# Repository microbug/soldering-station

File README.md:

# Soldering Station (Richard's Version)
A JBC-compatible open-source soldering station. Built for T245 tips.

## Hardware

## Firmware
An STM32CubeIDE project targetting an STM32L011F4Px.

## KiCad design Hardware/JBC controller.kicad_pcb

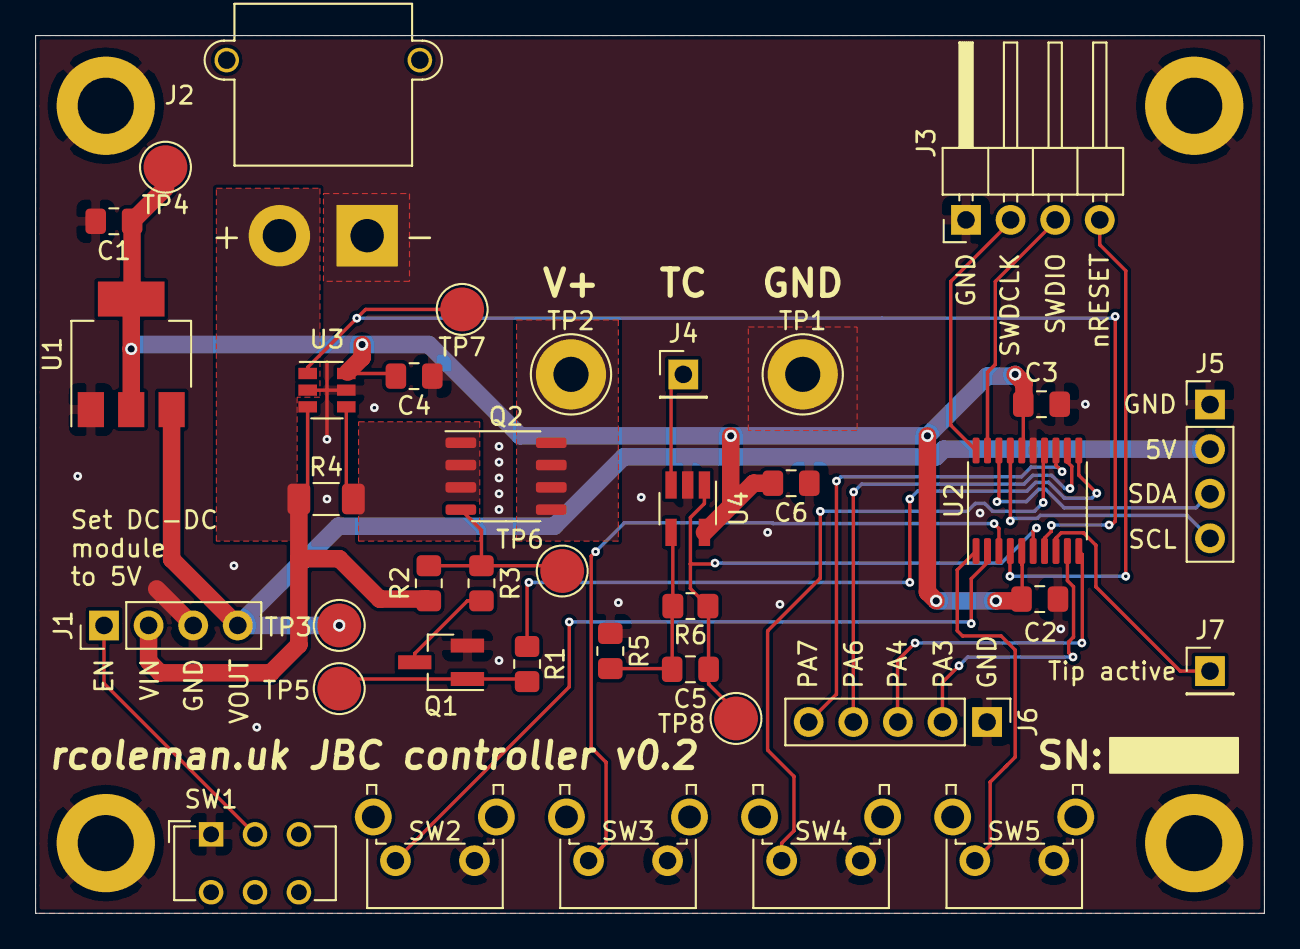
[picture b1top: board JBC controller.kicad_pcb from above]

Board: 2 copper layers, 70.0 x 50.0 mm, 42 parts (0 on the bottom side), 29 nets.

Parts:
C1: 10u; C_0805_2012Metric_Pad1.18x1.45mm_HandSolder
C2, C3, C4, C6: 100n; C_0805_2012Metric_Pad1.18x1.45mm_HandSolder
C5: 1n; C_0805_2012Metric_Pad1.18x1.45mm_HandSolder
H1, H2, H3, H4: MountingHole_Pad; MountingHole_3.2mm_M3_DIN965_Pad
J1, J5: Conn_01x04_Male; PinHeader_1x04_P2.54mm_Vertical
J2: XT30; AMASS_XT30PW-M_1x02_P2.50mm_Horizontal
J3: Conn_01x04_Male; PinHeader_1x04_P2.54mm_Horizontal
J4, J7: Conn_01x01_Male; PinHeader_1x01_P2.54mm_Vertical
J6: Conn_01x05_Male; PinHeader_1x05_P2.54mm_Vertical
Q1: BC846; SOT-23_Handsoldering
Q2: SI4101DY
R1: 10k; R_0805_2012Metric_Pad1.20x1.40mm_HandSolder
R2: 470; R_0805_2012Metric_Pad1.20x1.40mm_HandSolder
R3: 2k2; R_0805_2012Metric_Pad1.20x1.40mm_HandSolder
R4: 10m; R_1206_3216Metric_Pad1.30x1.75mm_HandSolder
R5: 100; R_0805_2012Metric_Pad1.20x1.40mm_HandSolder
R6: 20k; R_0805_2012Metric_Pad1.20x1.40mm_HandSolder
SW1: JS202011AQN; SW_CuK_JS202011AQN_DPDT_Angled
SW2, SW3, SW4, SW5: FSMRA3JH; SW_Tactile_SPST_Angled_PTS645Vx58-2LFS
TP1, TP2: TestPoint; TestPoint_Plated_Hole_D3.0mm
TP3, TP4, TP5, TP6, TP7, TP8: TestPoint; TestPoint_Pad_D2.5mm
U1: LM1117-3.3; SOT-223-3_TabPin2
U2: STM32L011F4Px; TSSOP-20_4.4x6.5mm_P0.65mm
U3: INA181A1; SOT-23-6
U4: AD8538AR; SOT-23-5_HandSoldering

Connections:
+3V3: C1.1, C2.1, C3.2, C4.2, C6.2, TP4.1, U1.2, U2.5, U2.16, U3.6, U4.5
+5V: J1.4, J5.2, TP3.1, U1.3
/BTN_DOWN: SW4.2, U2.14
/BTN_ENTER: SW5.2, U2.1
/BTN_MENU: SW2.2, U2.2
/BTN_UP: SW3.2, U2.3
/HEATER_CURRENT_AMP: TP7.1, U2.7, U3.1
/I2C_SCL: J5.4, U2.17
/I2C_SDA: J5.3, U2.18
/NRESET: J3.4, U2.4
/PA3: J6.2, U2.9
/PA4: J6.3, U2.10
/PA6: J6.4, U2.12
/PA7: J6.5, U2.13
/SWDCLK: J3.2, U2.20
/SWDIO: J3.3, U2.19
/TIP_ACTIVE: J7.1, U2.8
/TIP_PWM: R1.2, U2.11
/TIP_TC: J4.1, U4.3
/TIP_TC_AMP: C5.1, R6.1, TP8.1, U2.6, U4.1
/TIP_V+: Q2.3, TP2.1
GND: C1.2, C2.2, C3.1, C4.1, C6.1, H1.1, H2.1, H3.1, H4.1, J1.3, J2.1, J3.1, J5.1, J6.1, Q1.2, R5.1, SW1.1, SW2.1, SW3.1, SW4.1, SW5.1, TP1.1, U1.1, U2.15, U3.2, U3.5, U4.2
unnamed: C5.2, R5.2, R6.2, U4.4
unnamed: J1.1, SW1.2
unnamed: Q1.1, R1.1, TP5.1
unnamed: Q1.3, R3.2
unnamed: Q2.1, R4.2, U3.4
unnamed: Q2.2, R2.2, R3.1, TP6.1
VCC: J1.2, J2.2, R2.1, R4.1, U3.3

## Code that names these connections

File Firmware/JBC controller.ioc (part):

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Mcu.Name=STM32L011F(3-4)Px
Mcu.Package=TSSOP20
Mcu.UserName=STM32L011F4Px
PA0-CK_IN.GPIOParameters=GPIO_Label
PA0-CK_IN.GPIO_Label=TIP_TC_AMP
PA0-CK_IN.Mode=IN0
PA0-CK_IN.Signal=ADC_IN0
PA1.GPIOParameters=GPIO_Label
PA1.GPIO_Label=HEATER_CURRENT_AMP
PA1.Signal=ADC_IN1
PA10.GPIOParameters=GPIO_Pu
PA10.GPIO_Pu=GPIO_PULLUP
PA10.Mode=I2C
PA10.Signal=I2C1_SDA
PA13.Mode=Serial_Wire
PA13.Signal=SYS_SWDIO
PA14.Mode=Serial_Wire
PA14.Signal=SYS_SWCLK
PA2.GPIOParameters=GPIO_PuPd,GPIO_Label
PA2.GPIO_Label=TIP_ACTIVE
PA2.GPIO_PuPd=GPIO_PULLUP
PA2.Signal=GPIO_Input
PA3.GPIOParameters=GPIO_Label
PA3.GPIO_Label=OC_TEST
PA3.Signal=GPIO_Output
PA5.GPIOParameters=GPIO_Label
PA5.GPIO_Label=TIP_PWM
PA5.Signal=S_TIM2_CH1
PA9.GPIOParameters=GPIO_Pu
PA9.GPIO_Pu=GPIO_PULLUP
PA9.Mode=I2C
PA9.Signal=I2C1_SCL
PB1.GPIOParameters=GPIO_PuPd,GPIO_Label,GPIO_ModeDefaultEXTI
PB1.GPIO_Label=BTN_DOWN
PB1.GPIO_ModeDefaultEXTI=GPIO_MODE_IT_FALLING
PB1.GPIO_PuPd=GPIO_PULLUP
PB1.Signal=GPXTI1
PB9-BOOT0.GPIOParameters=GPIO_PuPd,GPIO_Label,GPIO_ModeDefaultEXTI
PB9-BOOT0.GPIO_Label=BTN_ENTER
PB9-BOOT0.GPIO_ModeDefaultEXTI=GPIO_MODE_IT_FALLING
PB9-BOOT0.GPIO_PuPd=GPIO_PULLUP
PB9-BOOT0.Signal=GPXTI9
PC14-OSC32_IN.GPIOParameters=GPIO_PuPd,GPIO_Label,GPIO_ModeDefaultEXTI
PC14-OSC32_IN.GPIO_Label=BTN_MENU
PC14-OSC32_IN.GPIO_ModeDefaultEXTI=GPIO_MODE_IT_FALLING
PC14-OSC32_IN.GPIO_PuPd=GPIO_PULLUP
PC14-OSC32_IN.Signal=GPXTI14
PC15-OSC32_OUT.GPIOParameters=GPIO_PuPd,GPIO_Label,GPIO_ModeDefaultEXTI
PC15-OSC32_OUT.GPIO_Label=BTN_UP
PC15-OSC32_OUT.GPIO_ModeDefaultEXTI=GPIO_MODE_IT_FALLING
PC15-OSC32_OUT.GPIO_PuPd=GPIO_PULLUP
PC15-OSC32_OUT.Signal=GPXTI15
RCC.HSE_VALUE=8000000
RCC.SYSCLKFreq_VALUE=32000000
RCC.SYSCLKSource=RCC_SYSCLKSOURCE_PLLCLK
board=custom

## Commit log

2021-08-08 Initial commit (board v0.1)
2024-01-17 Early firmware (before HAL update)
2024-02-28 Basic working firmware
2024-03-01 Remove backup files
2024-03-01 Hardware v0.1
2024-03-01 Exclude KiCad and FreeCAD backups
2024-03-01 Button cap test
2024-03-01 Simulate hardware v0.1
2024-03-01 Add license
2024-03-01 Remove Debug folder
2024-03-01 Add readme
2024-03-01 Another KiCad file
2024-03-01 Enable Markdown formatting
2024-03-02 Add no tool detection and ability to hold buttons
2024-03-03 Add LPUART reporting of tip temperature for PI(D) tuning
2024-03-05 Add tip inactive sleep and asymmetrical PID window
2024-03-05 LL ADC/DMA drivers to reduce code size
2024-03-07 Early CAD
2024-03-07 Better error messages, make LCD driver non-reliant on ISRs
2024-03-07 PSU datasheet
2025-08-29 Add EEPROM setpoint saving, increase display and button task frequency, update to latest CubeL0
